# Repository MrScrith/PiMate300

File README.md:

# PiMate300

This is a project to upgrade an Apple eMate 300 to become a modern laptop, it will be powered by a Raspberry Pi to allow upgrade flexability (when a new Pi comes out it should be possible to upgrade the Pi and keep the existing board).

It will start with passive cooling, with an eye to adding a tiny fan to the Right side in case that is not viable.

Hopefully, all original openings will be used (with new inserts for different ports) and minimal case modification would be needed.

At the moment the following items will need to be modified/removed from the case: 
- Battery Box (unless a powerful LiPro or similar battery can be found to fit there).
- Center mounting post (for accessability and asthetics the Pi will be placed in the center).

## The following tools will be used for this project:
| Tool | Version | Purpose |
|------|---------|---------|
| [KiCad](https://www.kicad-pcb.org/) | v5.1.5 | PCB Design and layout |
| **TBD** | **TBD** | 3D Modeling of inserts and supports |
| **TBD** | **TBD** | Programming of microprocessor used for Power Management and Keyboard USB HID |
| [Quartus II](https://fpgasoftware.intel.com/13.0sp1/?edition=subscription) | v13.0 SP 1 | Programming of FPGA for display |

# Eventually this will be sold as an almost-drop-in kit, at least that is the hope.

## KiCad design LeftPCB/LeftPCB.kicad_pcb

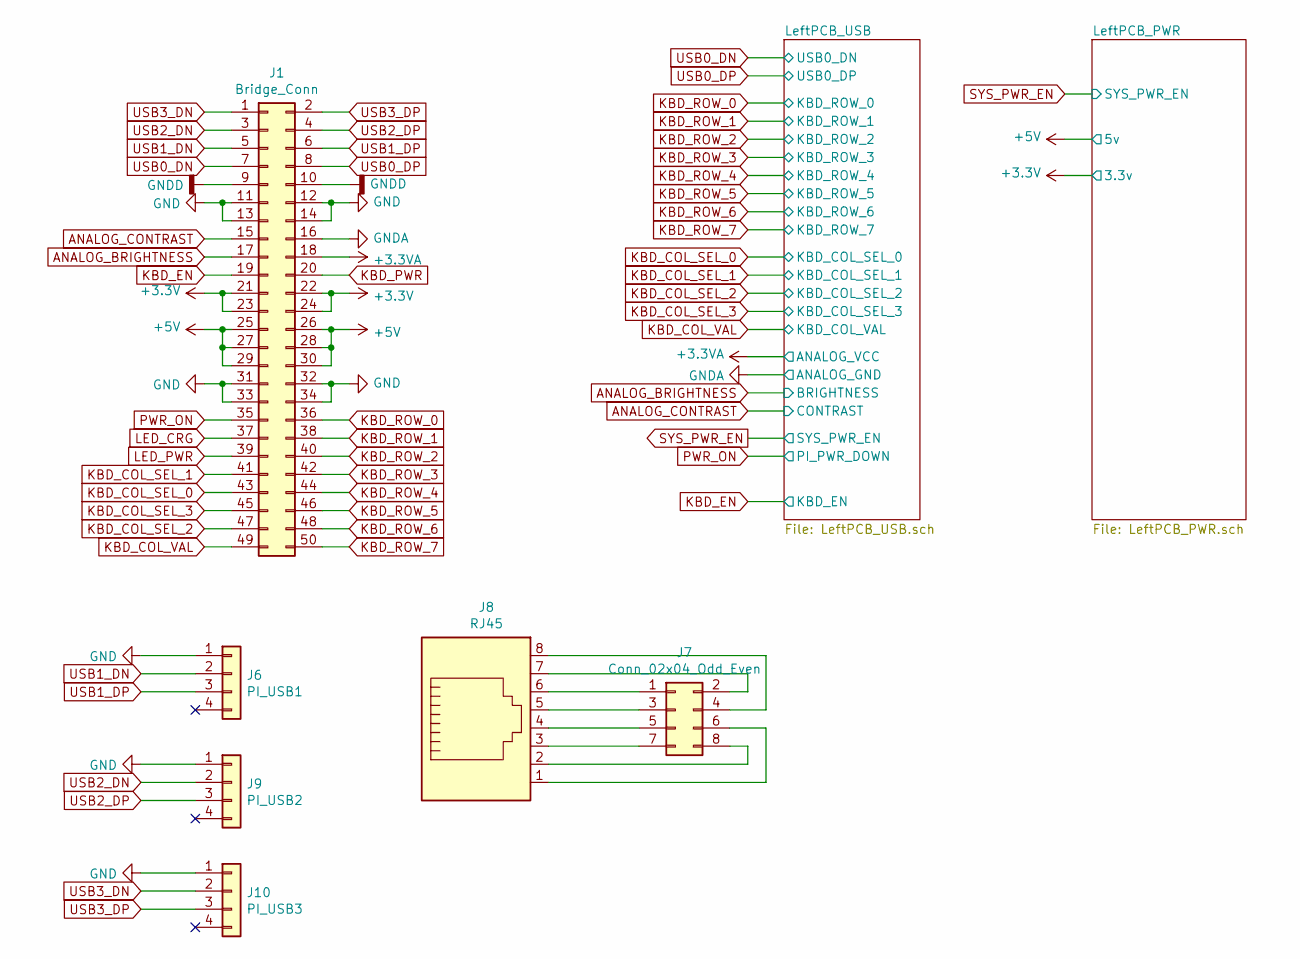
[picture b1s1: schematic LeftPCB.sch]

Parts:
J1: Bridge_Conn; Pin_Header_Straight_2x25_Pitch2.00mm
J6: PI_USB1; Pin_Header_Straight_1x04_Pitch1.00mm
J7: Conn_02x04_Odd_Even; Pin_Header_Straight_2x04_Pitch1.00mm
J8: RJ45; RJ45_8
J9: PI_USB2; Pin_Header_Straight_1x04_Pitch1.00mm
J10: PI_USB3; Pin_Header_Straight_1x04_Pitch1.00mm

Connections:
+3V3: J1.21, J1.22, J1.23, J1.24; also elsewhere on the board
+5V: J1.25, J1.26, J1.27, J1.28, J1.29, J1.30; also elsewhere on the board
ANALOG_BRIGHTNESS: J1.17; also elsewhere on the board
ANALOG_CONTRAST: J1.15; also elsewhere on the board
ANALOG_GND: J1.16; also elsewhere on the board
ANALOG_PWR: J1.18; also elsewhere on the board
GND: J1.11, J1.12, J1.13, J1.14, J1.31, J1.32, J1.33, J1.34, J6.1, J9.1, J10.1; also elsewhere on the board
GNDD: J1.9, J1.10; also elsewhere on the board
IS_PWR_DWN: J1.35; also elsewhere on the board
KBD_COL_SEL_0: J1.43; also elsewhere on the board
KBD_COL_SEL_1: J1.41; also elsewhere on the board
KBD_COL_SEL_2: J1.47; also elsewhere on the board
KBD_COL_SEL_3: J1.45; also elsewhere on the board
KBD_COL_VAL: J1.49; also elsewhere on the board
KBD_EN: J1.19; also elsewhere on the board
KBD_PWR: J1.20
KBD_ROW_0: J1.36; also elsewhere on the board
KBD_ROW_1: J1.38; also elsewhere on the board
KBD_ROW_2: J1.40; also elsewhere on the board
KBD_ROW_3: J1.42; also elsewhere on the board
KBD_ROW_4: J1.44; also elsewhere on the board
KBD_ROW_5: J1.46; also elsewhere on the board
KBD_ROW_6: J1.48; also elsewhere on the board
KBD_ROW_7: J1.50; also elsewhere on the board
LED_CRG: J1.37
LED_PWR: J1.39
unnamed: J7.1, J8.6
unnamed: J7.2, J8.7
unnamed: J7.3, J8.5
unnamed: J7.4, J8.8
unnamed: J7.5, J8.4
unnamed: J7.6, J8.1
unnamed: J7.7, J8.3
unnamed: J7.8, J8.2
USB0_DN: J1.7; also elsewhere on the board
USB0_DP: J1.8; also elsewhere on the board
USB1_DN: J1.5, J6.2
USB1_DP: J1.6, J6.3
USB2_DN: J1.3, J9.2
USB2_DP: J1.4, J9.3
USB3_DN: J1.1, J10.2
USB3_DP: J1.2, J10.3

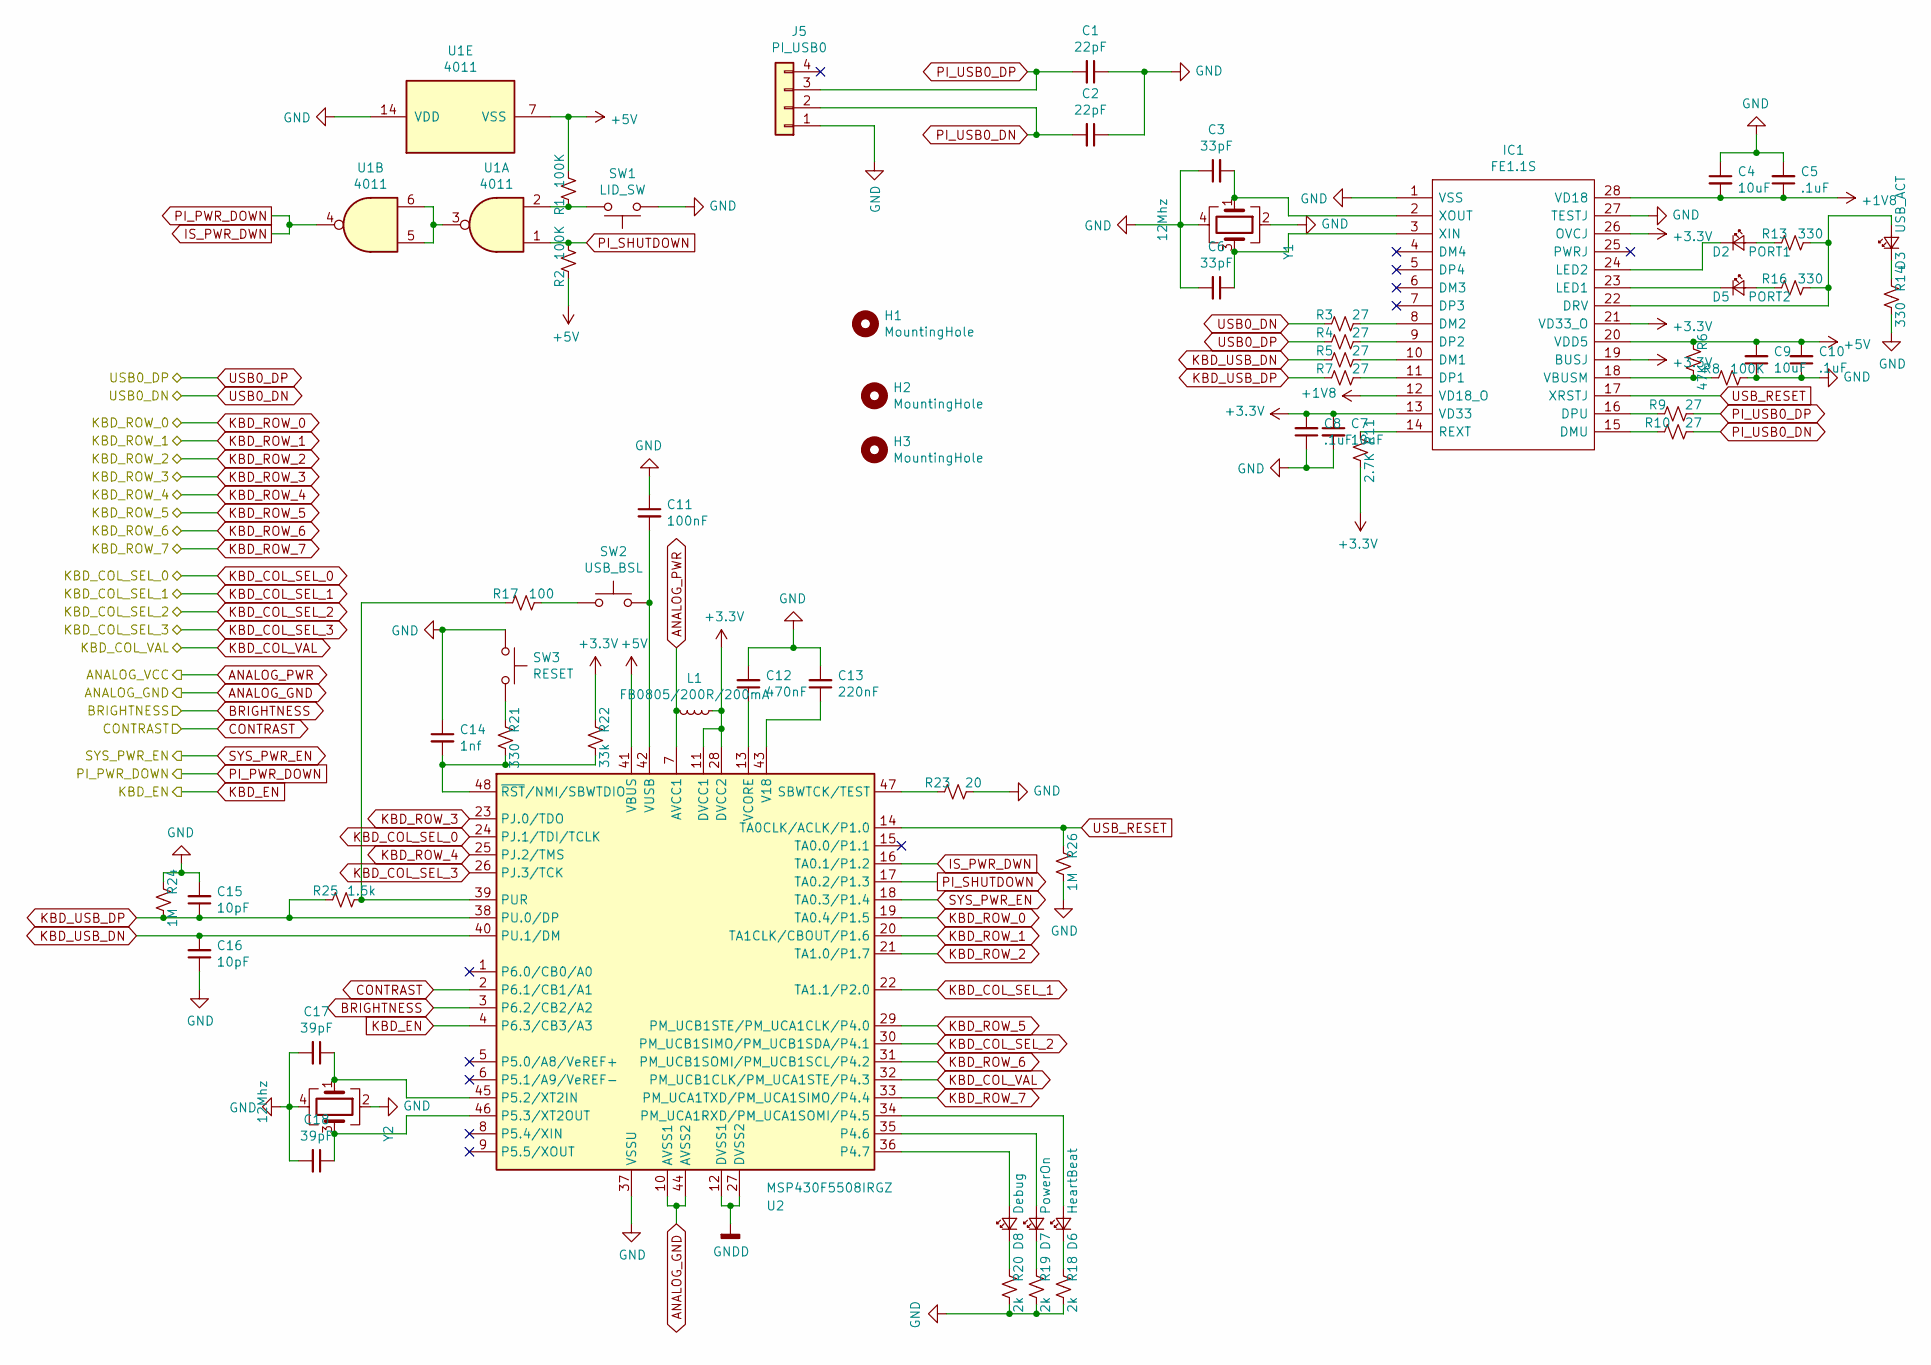
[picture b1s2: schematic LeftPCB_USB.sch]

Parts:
C1, C2: 22pF; C_0603
C3, C6: 33pF; C_0603
C4, C7, C9: 10uF; C_0603
C5, C8, C10: .1uF; C_0603
C11: 100nF; C_0603
C12: 470nF; C_0603
C13: 220nF; C_0603
C14: 1nf; C_0603
C15, C16: 10pF; C_0603
C17, C18: 39pF; C_0603
D2: PORT1; LED_0805
D3: USB_ACT; LED_0805
D5: PORT2; LED_0805
D6: HeartBeat; LED_0805
D7: PowerOn; LED_0805
D8: Debug; LED_0805
H1, H2, H3: MountingHole; MountingHole_2.7mm
IC1: FE1.1S; SOP64P600X175-28N; Manufacturer_Part_Number FE1.1S
J5: PI_USB0; Pin_Header_Straight_1x04_Pitch1.00mm
L1: FB0805/200R/200mA; L_0805
R1, R2, R8: 100K; R_0603
R3, R4, R5, R7, R9, R10: 27; R_0603
R6: 47K; R_0603
R11: 2.7K; R_0603
R13, R14, R16, R21: 330; R_0603
R17: 100; R_0603
R18, R19, R20: 2k; R_0603
R22: 33k; R_0603
R23: 20; R_0603
R24, R26: 1M; R_0603
R25: 1.5k; R_0603
SW1: LID_SW; SW_SPST_B3S-1000
SW2: USB_BSL; SW_SPST_B3S-1000
SW3: RESET; SW_SPST_B3S-1000
U1: 4011; SOIC-14_3.9x8.7mm_Pitch1.27mm
U2: MSP430F5508IRGZ; LQFP-48_7x7mm_Pitch0.5mm
Y1, Y2: 12Mhz; Oscillator_SMD_EuroQuartz_XO53-4pin_5.0x3.2mm

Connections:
+1V8: C4.2, C5.1, IC1.12 (VD18_O), IC1.28 (VD18)
+3V3: C7.1, C8.2, IC1.13 (VD33), IC1.19 (BUSJ), IC1.21 (VD33_O), IC1.26 (OVCJ), L1.1, R11.1, R22.2, U2.11 (DVCC1), U2.28 (DVCC2); also elsewhere on the board
+5V: C9.2, C10.2, IC1.20 (VDD5), R1.1, R2.2, R6.2, U1.7 (VSS), U2.41 (VBUS); also elsewhere on the board
ANALOG_BRIGHTNESS: U2.3 (P6.2/CB2/A2); also elsewhere on the board
ANALOG_CONTRAST: U2.2 (P6.1/CB1/A1); also elsewhere on the board
ANALOG_GND: U2.10 (AVSS1), U2.44 (AVSS2); also elsewhere on the board
ANALOG_PWR: L1.2, U2.7 (AVCC1); also elsewhere on the board
GND: C1.1, C2.1, C3.1, C4.1, C5.2, C6.2, C7.2, C8.1, C9.1, C10.1, C11.1, C12.2, C13.2, C14.1, C15.2, C16.1, C17.2, C18.2, IC1.1 (VSS), IC1.27 (TESTJ), J5.1, R8.1, R14.1, R18.1, R19.1, R20.1, R23.1, R24.2, R26.1, SW1.1, SW3.1, U1.14 (VDD), U2.37 (VSSU), Y1.2, Y1.4, Y2.2, Y2.4; also elsewhere on the board
GNDD: U2.12 (DVSS1), U2.27 (DVSS2); also elsewhere on the board
IS_PWR_DWN: U1.4, U2.16 (TA0.1/P1.2); also elsewhere on the board
KBD_COL_SEL_0: U2.24 (PJ.1/TDI/TCLK); also elsewhere on the board
KBD_COL_SEL_1: U2.22 (TA1.1/P2.0); also elsewhere on the board
KBD_COL_SEL_2: U2.30 (PM_UCB1SIMO/PM_UCB1SDA/P4.1); also elsewhere on the board
KBD_COL_SEL_3: U2.26 (PJ.3/TCK); also elsewhere on the board
KBD_COL_VAL: U2.32 (PM_UCB1CLK/PM_UCA1STE/P4.3); also elsewhere on the board
KBD_EN: U2.4 (P6.3/CB3/A3); also elsewhere on the board
KBD_ROW_0: U2.19 (TA0.4/P1.5); also elsewhere on the board
KBD_ROW_1: U2.20 (TA1CLK/CBOUT/P1.6); also elsewhere on the board
KBD_ROW_2: U2.21 (TA1.0/P1.7); also elsewhere on the board
KBD_ROW_3: U2.23 (PJ.0/TDO); also elsewhere on the board
KBD_ROW_4: U2.25 (PJ.2/TMS); also elsewhere on the board
KBD_ROW_5: U2.29 (PM_UCB1STE/PM_UCA1CLK/P4.0); also elsewhere on the board
KBD_ROW_6: U2.31 (PM_UCB1SOMI/PM_UCB1SCL/P4.2); also elsewhere on the board
KBD_ROW_7: U2.33 (PM_UCA1TXD/PM_UCA1SIMO/P4.4); also elsewhere on the board
KBD_USB_DN: C16.2, R5.2, U2.40 (PU.1/DM)
KBD_USB_DP: C15.1, R7.2, R24.1, R25.2, U2.38 (PU.0/DP)
unnamed: C3.2, IC1.2 (XOUT), Y1.1
unnamed: C6.1, IC1.3 (XIN), Y1.3
unnamed: C11.2, SW2.2, U2.42 (VUSB)
unnamed: C12.1, U2.13 (VCORE)
unnamed: C13.1, U2.43 (V18)
unnamed: C14.2, R21.1, R22.1, U2.48 (~RST~/NMI/SBWTDIO)
unnamed: C17.1, U2.45 (P5.2/XT2IN), Y2.1
unnamed: C18.1, U2.46 (P5.3/XT2OUT), Y2.3
unnamed: D2.1 (K), IC1.24 (LED2)
unnamed: D2.2 (A), R13.2
unnamed: D3.1 (K), R14.2
unnamed: D3.2 (A), IC1.22 (DRV), R13.1, R16.1
unnamed: D5.1 (K), IC1.23 (LED1)
unnamed: D5.2 (A), R16.2
unnamed: D6.1 (K), R18.2
unnamed: D6.2 (A), U2.34 (PM_UCA1RXD/PM_UCA1SOMI/P4.5)
unnamed: D7.1 (K), R19.2
unnamed: D7.2 (A), U2.35 (P4.6)
unnamed: D8.1 (K), R20.2
unnamed: D8.2 (A), U2.36 (P4.7)
unnamed: IC1.8 (DM2), R3.1
unnamed: IC1.9 (DP2), R4.1
unnamed: IC1.10 (DM1), R5.1
unnamed: IC1.11 (DP1), R7.1
unnamed: IC1.14 (REXT), R11.2
unnamed: IC1.15 (DMU), R10.2
unnamed: IC1.16 (DPU), R9.2
unnamed: IC1.18 (VBUSM), R6.1, R8.2
unnamed: R1.2, SW1.2, U1.2
unnamed: R17.1, SW2.1
unnamed: R17.2, R25.1, U2.39 (PUR)
unnamed: R21.2, SW3.2
unnamed: R23.2, U2.47 (SBWTCK/TEST)
unnamed: U1.3, U1.5, U1.6
PI_SHUTDOWN: R2.1, U1.1, U2.17 (TA0.2/P1.3)
PI_USB0_DN: C2.2, J5.2, R10.1
PI_USB0_DP: C1.2, J5.3, R9.1
SYS_PWR_EN: U2.18 (TA0.3/P1.4); also elsewhere on the board
USB0_DN: R3.2; also elsewhere on the board
USB0_DP: R4.2; also elsewhere on the board
USB_RESET: IC1.17 (XRSTJ), R26.2, U2.14 (TA0CLK/ACLK/P1.0)

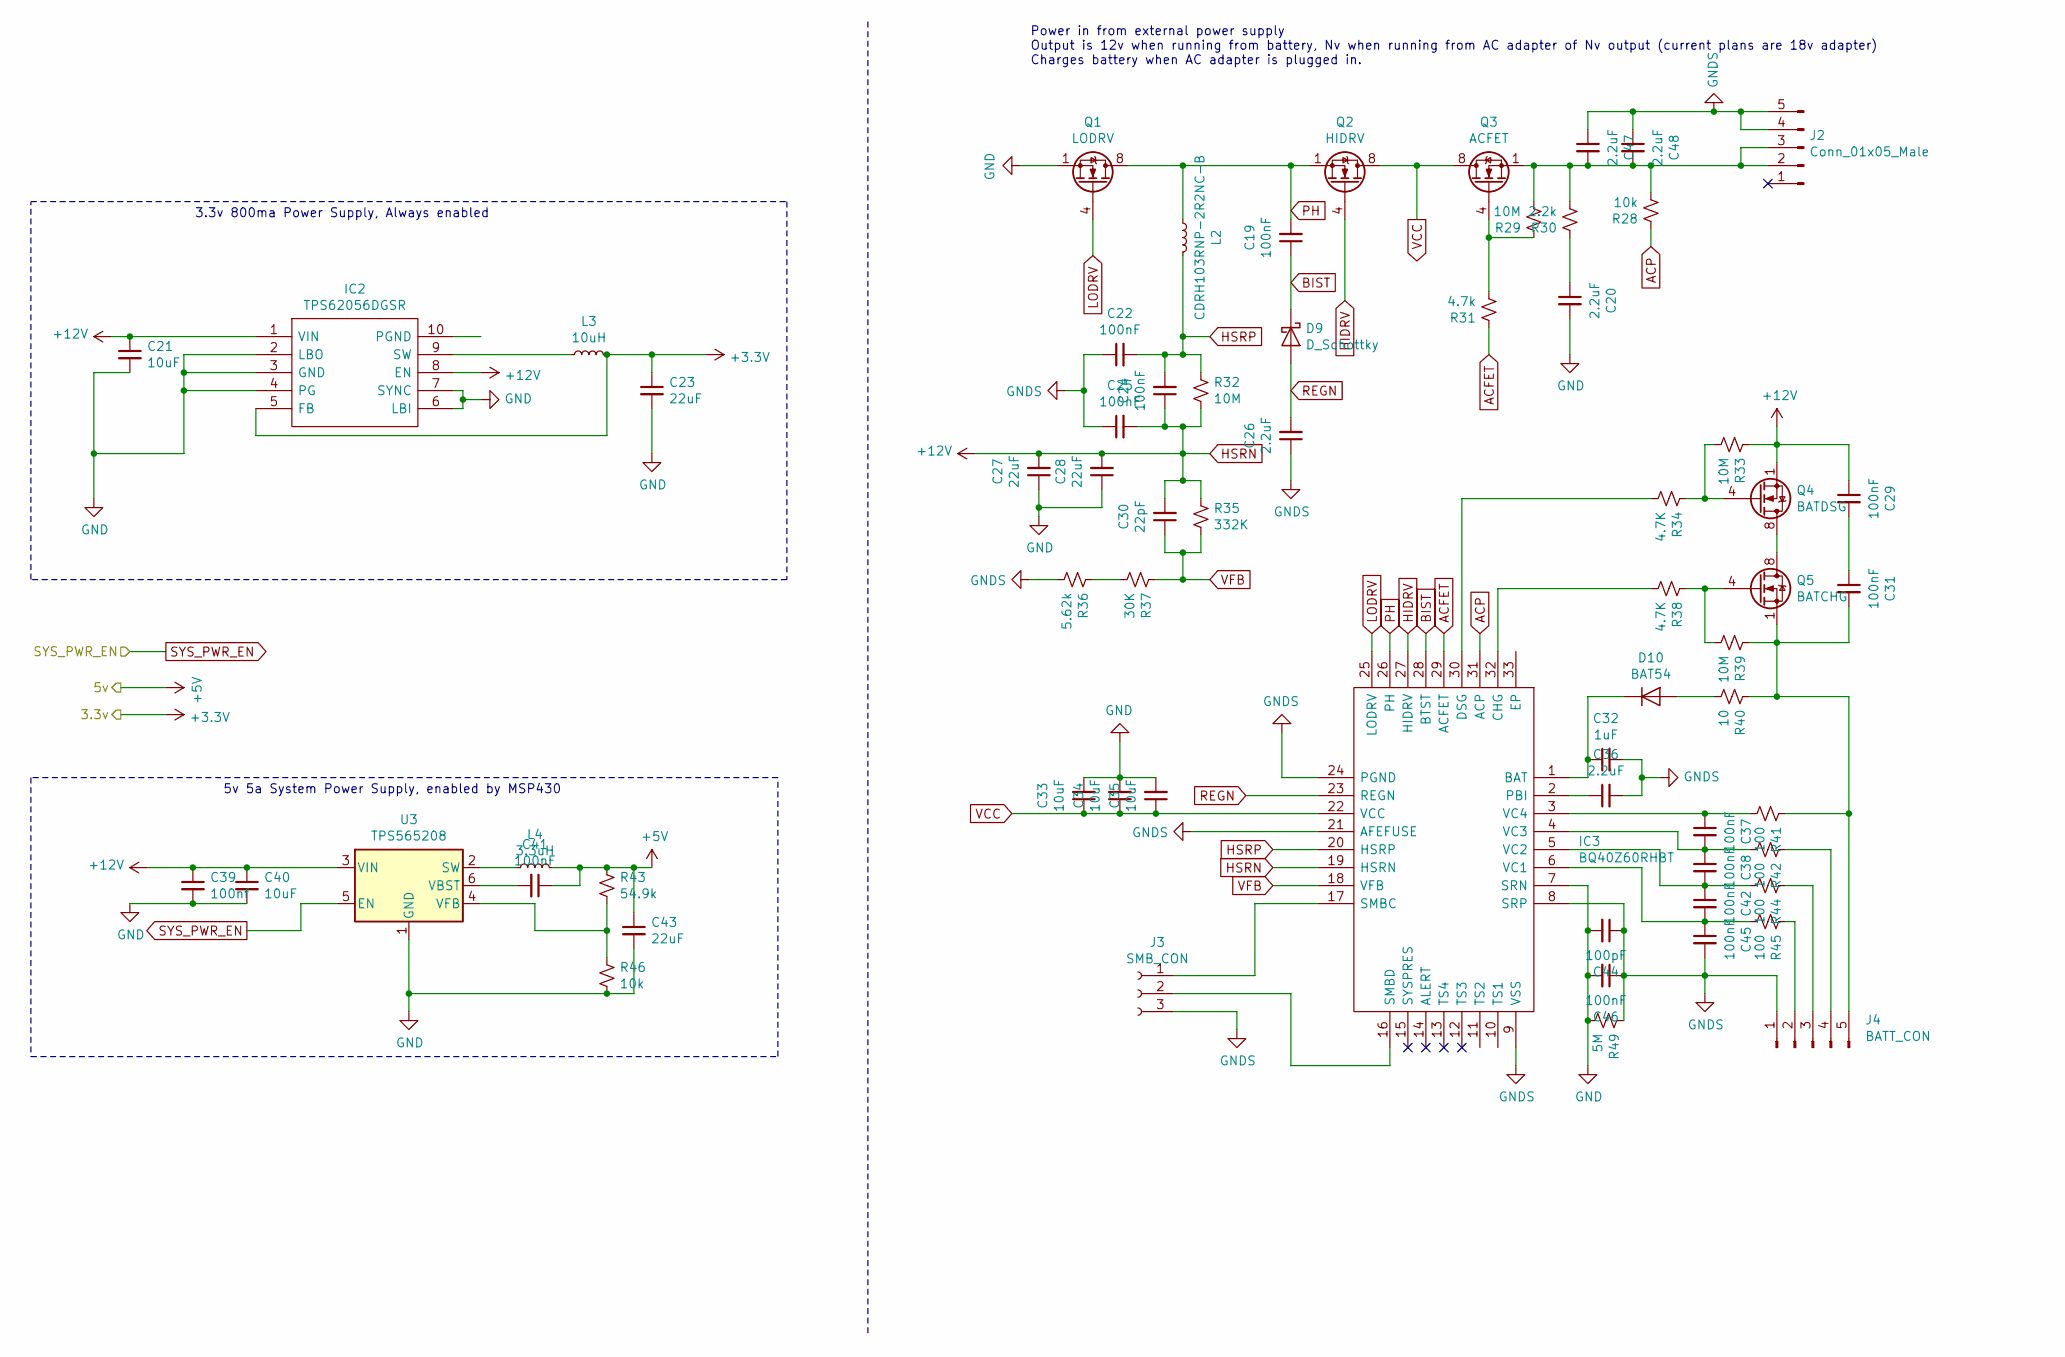
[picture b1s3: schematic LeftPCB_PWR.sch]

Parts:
C19, C22, C24, C25, C29, C31, C37, C38, C41, C42, C45, C46: 100nF; C_0603
C20, C26, C36, C47, C48: 2.2uF; C_0603
C21, C33, C34, C35, C40: 10uF; C_0603
C23, C27, C28, C43: 22uF; C_0603
C30: 22pF; C_0603
C32: 1uF; C_0603
C39: 100nf; C_0603
C44: 100pF; C_0603
D9: D_Schottky; D_0603
D10: BAT54; D_0603
IC2: TPS62056DGSR; SOP50P490X110-10N; Manufacturer_Part_Number TPS62056DGSR; Mouser Part Number 595-TPS62056DGSR
IC3: BQ40Z60RHBT; QFN50P500X500X100-33N-D; Manufacturer_Part_Number BQ40Z60RHBT; Mouser Part Number 595-BQ40Z60RHBT
J2: Conn_01x05_Male; Pin_Header_Straight_1x05_Pitch1.00mm
J3: SMB_CON; Pin_Header_Straight_1x03_Pitch1.00mm
J4: BATT_CON; Pin_Header_Straight_1x05_Pitch1.00mm
L2: CDRH103RNP-2R2NC-B; L_Vishay_IHLP-2020
L3: 10uH; L_0603
L4: 3.3uH; L_0603
Q1: LODRV; SOIC-8-N
Q2: HIDRV; SOIC-8-N
Q3: ACFET; SOIC-8-N
Q4: BATDSG; SOIC-8-N
Q5: BATCHG; SOIC-8-N
R28, R46: 10k; R_0603
R29, R32, R33, R39: 10M; R_0603
R30: 2.2k; R_0603
R31: 4.7k; R_0603
R34, R38: 4.7K; R_0603
R35: 332K; R_0603
R36: 5.62k; R_0603
R37: 30K; R_0603
R40: 10; R_0603
R41, R42, R44, R45: 100; R_0603
R43: 54.9k; R_0603
R49: 5M; R_2010
U3: TPS565208; SOT95P280X110-6N

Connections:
+3V3: C23.1, IC2.5 (FB), L3.2; also elsewhere on the board
+5V: C41.1, C43.1, L4.2, R43.2; also elsewhere on the board
ACFET: IC3.29 (ACFET), R31.1
ACP: IC3.31 (ACP), R28.1
BIST: C19.1, D9.1 (K), IC3.28 (BTST)
GND: C20.2, C21.2, C23.2, C27.1, C28.1, C33.2, C34.2, C35.2, C39.2, C40.2, C43.2, C44.2, C46.2, IC2.2 (LBO), IC2.3 (GND), IC2.4 (PG), IC2.6 (LBI), IC2.7 (SYNC), IC3.7 (SRN), Q1.1 (S), Q1.2 (S), Q1.3 (S), R46.1, R49.2, U3.1 (GND); also elsewhere on the board
GNDS: C22.1, C25.1, C26.1, C32.2, C36.2, C44.1, C45.2, C46.1, C47.1, C48.1, IC3.8 (SRP), IC3.9 (VSS), IC3.21 (AFEFUSE), IC3.24 (PGND), J2.4, J2.5, J3.3, J4.1, R36.2, R49.1
HIDRV: IC3.27 (HIDRV), Q2.4 (G)
HSRN: C21.1, C24.1, C25.2, C27.2, C28.2, C29.1, C30.2, C39.1, C40.1, IC2.1 (VIN), IC2.8 (EN), IC3.19 (HSRN), Q4.1 (S), Q4.2 (S), Q4.3 (S), R32.2, R33.1, R35.1, U3.3 (VIN)
HSRP: C22.2, C24.2, IC3.20 (HSRP), L2.2, R32.1
LODRV: IC3.25 (LODRV), Q1.4 (G)
unnamed: C20.1, R30.1
unnamed: C29.2, C31.1
unnamed: C31.2, J4.5, Q5.1 (S), Q5.2 (S), Q5.3 (S), R39.1, R40.1, R41.1
unnamed: C32.1, D10.1 (K), IC3.1 (BAT)
unnamed: C36.1, IC3.2 (PBI)
unnamed: C37.1, IC3.3 (VC4), R41.2
unnamed: C37.2, C38.1, IC3.4 (VC3), R42.2
unnamed: C38.2, C42.1, IC3.5 (VC2), R44.2
unnamed: C41.2, U3.6 (VBST)
unnamed: C42.2, C45.1, IC3.6 (VC1), R45.2
unnamed: C47.2, C48.2, J2.2, J2.3, Q3.1 (S), Q3.2 (S), Q3.3 (S), R28.2, R29.2, R30.2
unnamed: D10.2 (A), R40.2
unnamed: IC2.9 (SW), L3.1
unnamed: IC3.16 (SMBD), J3.2
unnamed: IC3.17 (SMBC), J3.1
unnamed: IC3.30 (DSG), R34.2
unnamed: IC3.32 (CHG), R38.2
unnamed: J4.2, R45.1
unnamed: J4.3, R44.1
unnamed: J4.4, R42.1
unnamed: L4.1, U3.2 (SW)
unnamed: Q3.4 (G), R29.1, R31.2
unnamed: Q4.4 (G), R33.2, R34.1
unnamed: Q4.5 (D), Q4.6 (D), Q4.7 (D), Q4.8 (D), Q5.5 (D), Q5.6 (D), Q5.7 (D), Q5.8 (D)
unnamed: Q5.4 (G), R38.1, R39.2
unnamed: R36.1, R37.2
unnamed: R43.1, R46.2, U3.4 (VFB)
PH: C19.2, IC3.26 (PH), L2.1, Q1.5 (D), Q1.6 (D), Q1.7 (D), Q1.8 (D), Q2.1 (S), Q2.2 (S), Q2.3 (S)
REGN: C26.2, D9.2 (A), IC3.23 (REGN)
SYS_PWR_EN: U3.5 (EN); also elsewhere on the board
VCC: C33.1, C34.1, C35.1, IC3.22 (VCC), Q2.5 (D), Q2.6 (D), Q2.7 (D), Q2.8 (D), Q3.5 (D), Q3.6 (D), Q3.7 (D), Q3.8 (D)
VFB: C30.1, IC3.18 (VFB), R35.2, R37.1

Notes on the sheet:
Power in from external power supply Output is 12v when running from battery, Nv when running from AC adapter of Nv output (current plans are 18v adapter) Charges battery when AC adapter is plugged in.
5v 5a System Power Supply, enabled by MSP430
3.3v 800ma Power Supply, Always enabled

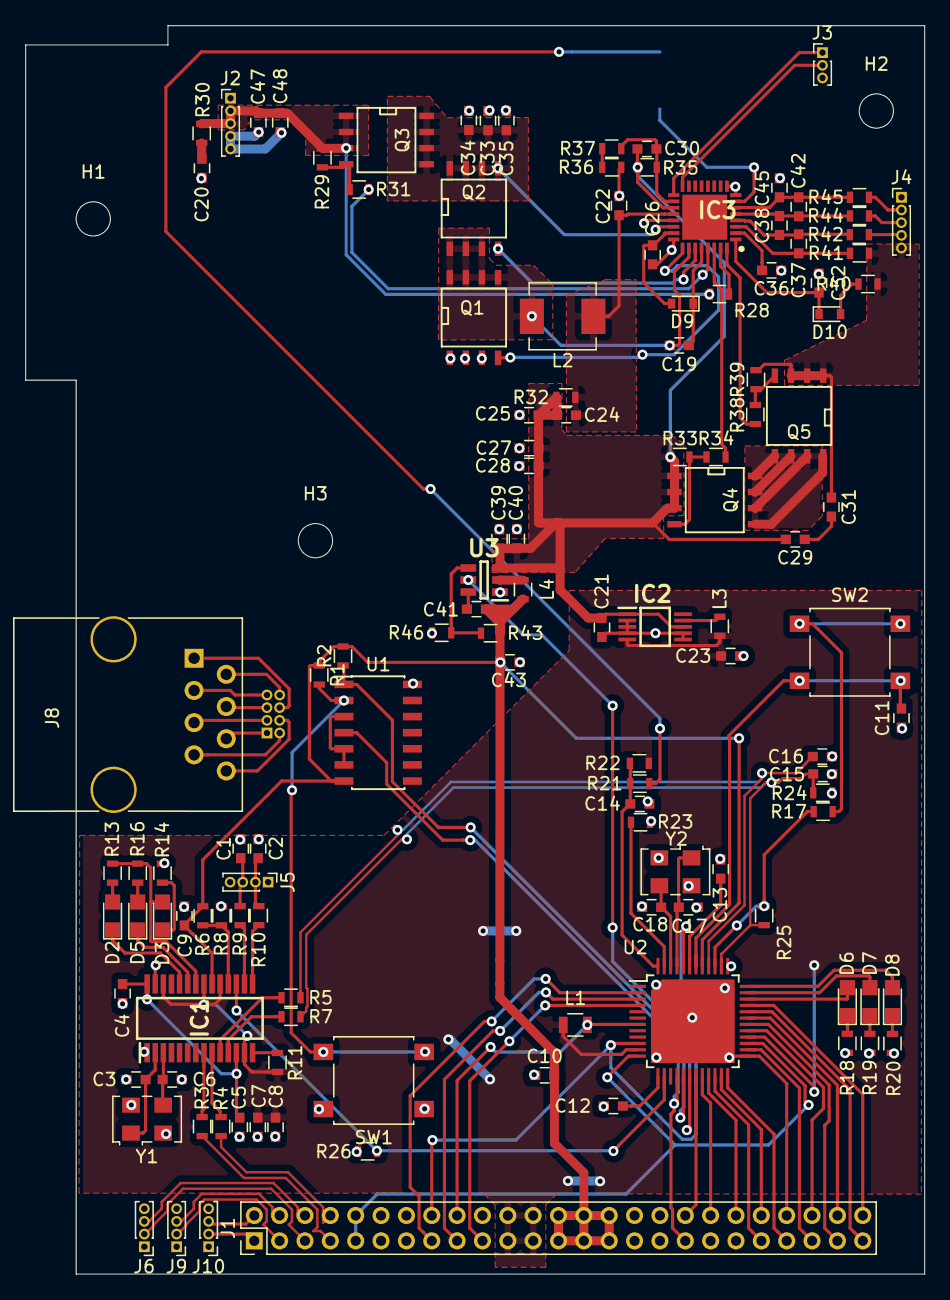
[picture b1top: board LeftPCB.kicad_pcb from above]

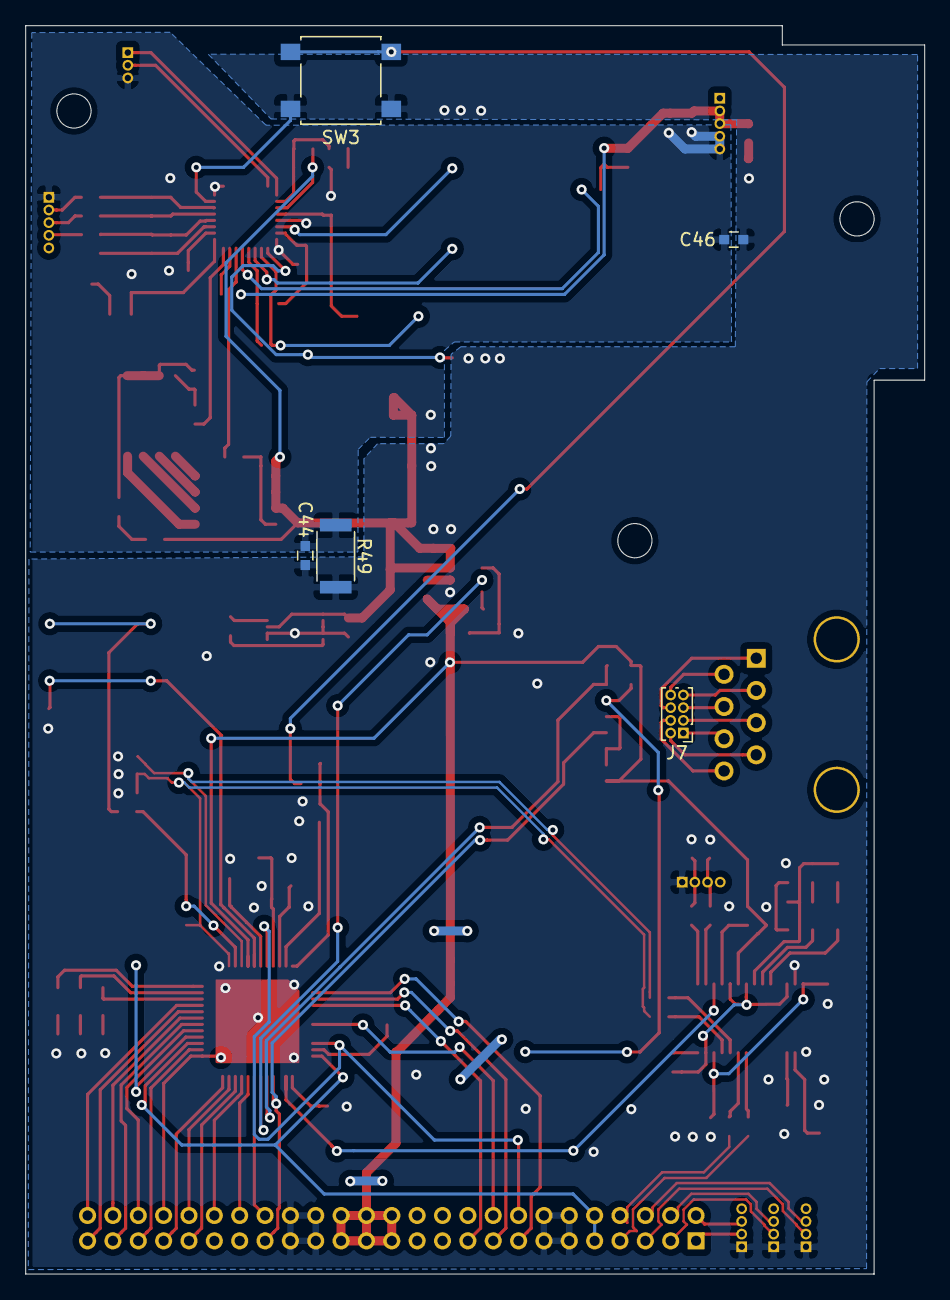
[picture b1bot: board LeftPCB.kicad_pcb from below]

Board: 2 copper layers, 70.9 x 98.5 mm, 133 parts (5 on the bottom side), 120 nets.

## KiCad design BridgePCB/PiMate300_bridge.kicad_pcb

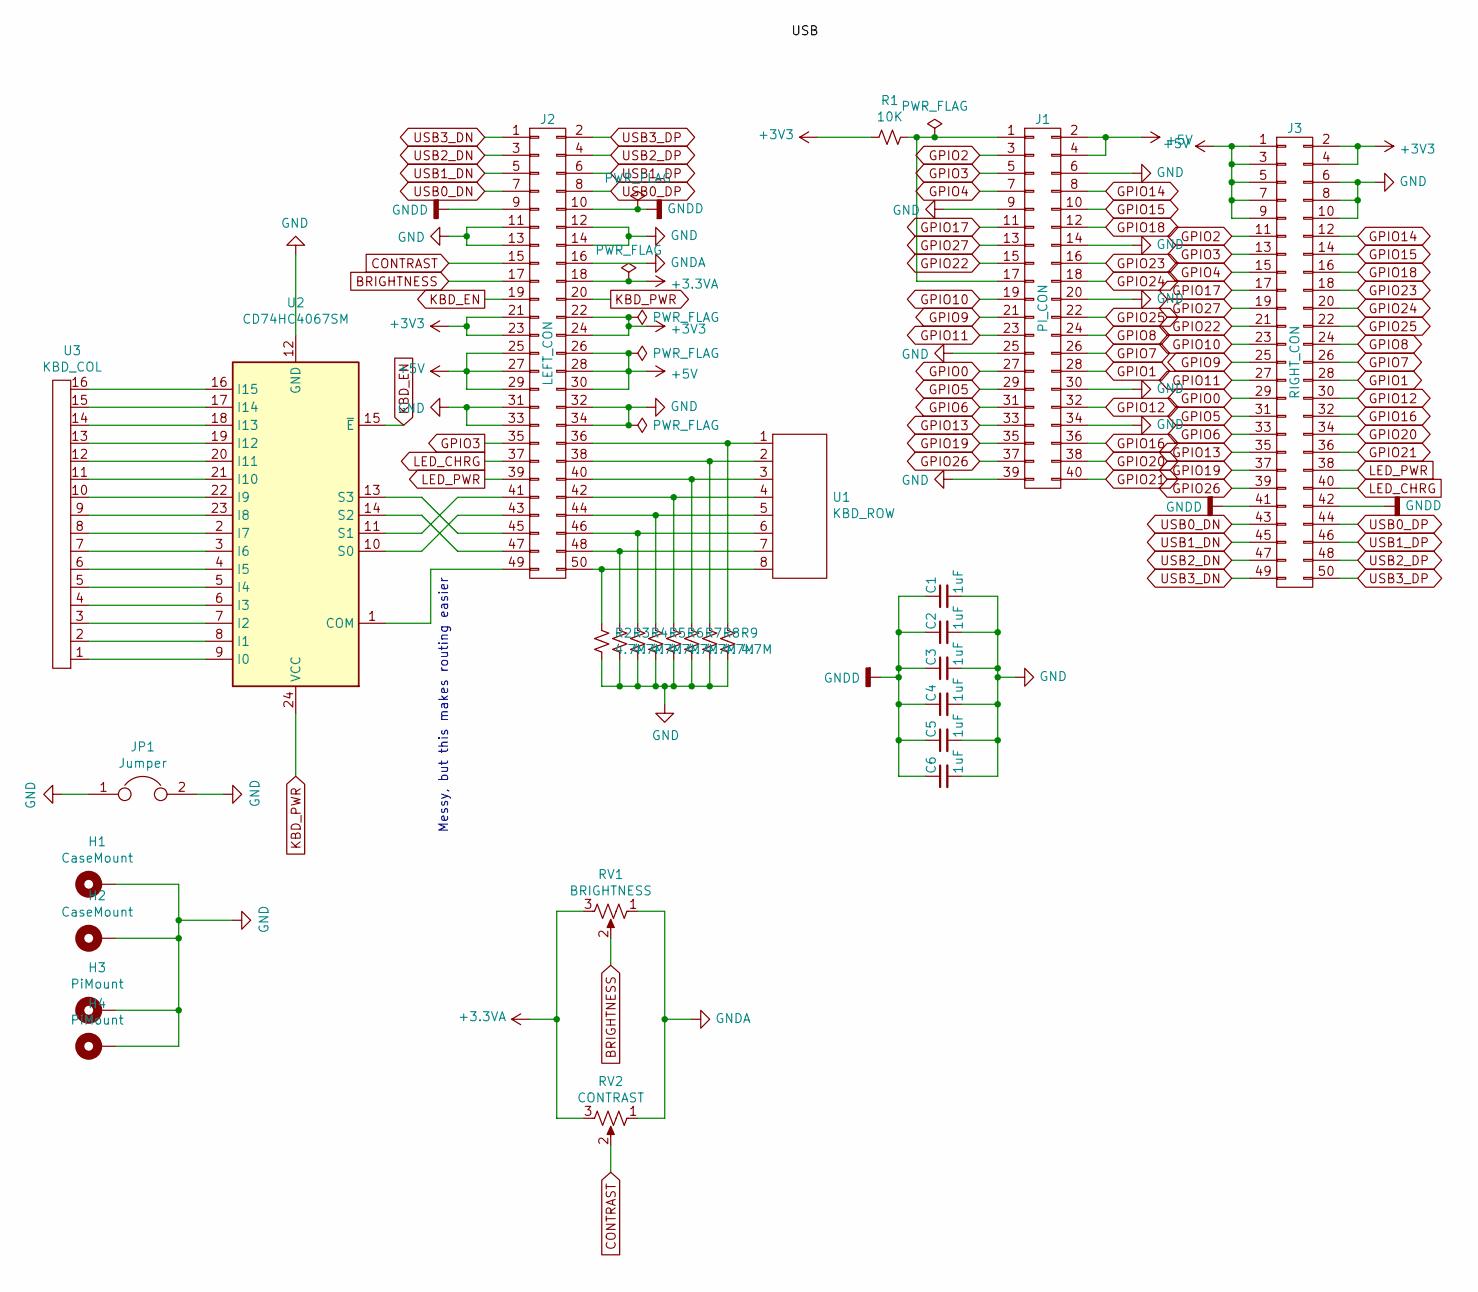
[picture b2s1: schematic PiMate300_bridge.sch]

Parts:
C1, C2, C3, C4, C5, C6: 1uF; C_0603_HandSoldering
H1, H2: CaseMount; MountingHole_3.2mm_M3_DIN965
H3, H4: PiMount; MountingHole_2.7mm_Pad
J1: PI_CON; Socket_Strip_Straight_2x20_Pitch2.54mm
J2: LEFT_CON; Socket_Strip_Angled_2x25_Pitch2.00mm
J3: RIGHT_CON; Socket_Strip_Angled_2x25_Pitch2.00mm
JP1: Jumper; NetTie-I
R1: 10K; R_0603_HandSoldering
R2, R3, R4, R5, R6, R7, R8, R9: 4.7M; R_0603_HandSoldering
RV1: BRIGHTNESS; PTA1543
RV2: CONTRAST; PTA1543
U1: KBD_ROW; FH12-08S-1SH
U2: CD74HC4067SM; CD74HC4067
U3: KBD_COL; FH12-16S-1SH

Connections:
+3.3VA: J2.18, RV1.3, RV2.3
+3V3: J2.21, J2.22, J2.23, J2.24, J3.2, J3.4, R1.2
+5V: J1.2, J1.4, J2.25, J2.26, J2.27, J2.28, J2.29, J2.30, J3.1, J3.3, J3.5, J3.7, J3.9
BRIGHTNESS: J2.17, RV1.2
CONTRAST: J2.15, RV2.2
GND: C1.2, C2.2, C3.2, C4.2, C5.2, C6.2, H1.1, H2.1, H3.1, H4.1, J1.6, J1.9, J1.14, J1.20, J1.25, J1.30, J1.34, J1.39, J2.11, J2.12, J2.13, J2.14, J2.31, J2.32, J2.33, J2.34, J3.6, J3.8, J3.10, JP1.1, JP1.2, R2.2, R3.2, R4.2, R5.2, R6.2, R7.2, R8.2, R9.2, U2.12 (GND)
GNDA: J2.16, RV1.1, RV2.1
GNDD: C1.1, C2.1, C3.1, C4.1, C5.1, C6.1, J2.9, J2.10, J3.41, J3.42
GPIO0: J1.27, J3.29
GPIO1: J1.28, J3.28
GPIO2: J1.3, J3.11
GPIO3: J1.5, J2.35, J3.13
GPIO4: J1.7, J3.15
GPIO5: J1.29, J3.31
GPIO6: J1.31, J3.33
GPIO7: J1.26, J3.26
GPIO8: J1.24, J3.24
GPIO9: J1.21, J3.25
GPIO10: J1.19, J3.23
GPIO11: J1.23, J3.27
GPIO12: J1.32, J3.30
GPIO13: J1.33, J3.35
GPIO14: J1.8, J3.12
GPIO15: J1.10, J3.14
GPIO16: J1.36, J3.32
GPIO17: J1.11, J3.17
GPIO18: J1.12, J3.16
GPIO19: J1.35, J3.37
GPIO20: J1.38, J3.34
GPIO21: J1.40, J3.36
GPIO22: J1.15, J3.21
GPIO23: J1.16, J3.18
GPIO24: J1.18, J3.20
GPIO25: J1.22, J3.22
GPIO26: J1.37, J3.39
GPIO27: J1.13, J3.19
KBD_EN: J2.19, U2.15 (~E)
KBD_PWR: J2.20, U2.24 (VCC)
LED_CHRG: J2.37, J3.40
LED_PWR: J2.39, J3.38
unnamed: J1.1, J1.17, R1.1
unnamed: J2.36, R9.1, U1.1
unnamed: J2.38, R8.1, U1.2
unnamed: J2.40, R7.1, U1.3
unnamed: J2.41, U2.11 (S1)
unnamed: J2.42, R6.1, U1.4
unnamed: J2.43, U2.10 (S0)
unnamed: J2.44, R5.1, U1.5
unnamed: J2.45, U2.13 (S3)
unnamed: J2.46, R4.1, U1.6
unnamed: J2.47, U2.14 (S2)
unnamed: J2.48, R3.1, U1.7
unnamed: J2.49, U2.1 (COM)
unnamed: J2.50, R2.1, U1.8
unnamed: U2.2 (I7), U3.8
unnamed: U2.3 (I6), U3.7
unnamed: U2.4 (I5), U3.6
unnamed: U2.5 (I4), U3.5
unnamed: U2.6 (I3), U3.4
unnamed: U2.7 (I2), U3.3
unnamed: U2.8 (I1), U3.2
unnamed: U2.9 (I0), U3.1
unnamed: U2.16 (I15), U3.16
unnamed: U2.17 (I14), U3.15
unnamed: U2.18 (I13), U3.14
unnamed: U2.19 (I12), U3.13
unnamed: U2.20 (I11), U3.12
unnamed: U2.21 (I10), U3.11
unnamed: U2.22 (I9), U3.10
unnamed: U2.23 (I8), U3.9
USB0_DN: J2.7, J3.43
USB0_DP: J2.8, J3.44
USB1_DN: J2.5, J3.45
USB1_DP: J2.6, J3.46
USB2_DN: J2.3, J3.47
USB2_DP: J2.4, J3.48
USB3_DN: J2.1, J3.49
USB3_DP: J2.2, J3.50

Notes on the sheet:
Messy, but this makes routing easier

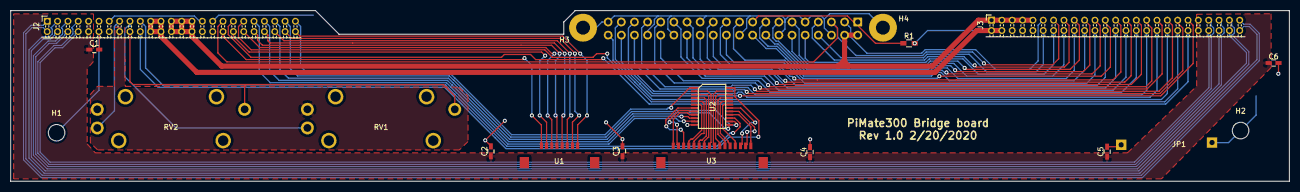
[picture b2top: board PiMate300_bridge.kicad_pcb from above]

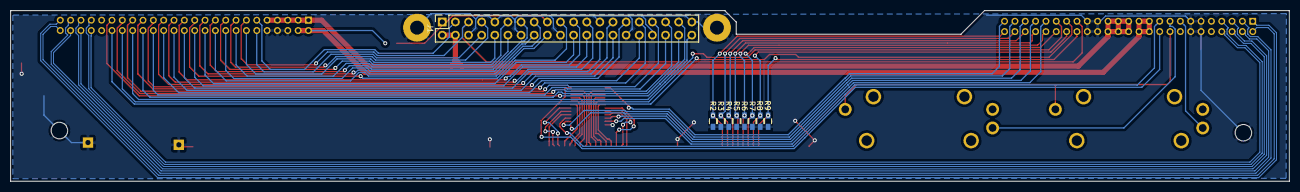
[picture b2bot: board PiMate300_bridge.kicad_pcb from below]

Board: 2 copper layers, 247.3 x 33.0 mm, 28 parts (9 on the bottom side), 78 nets.

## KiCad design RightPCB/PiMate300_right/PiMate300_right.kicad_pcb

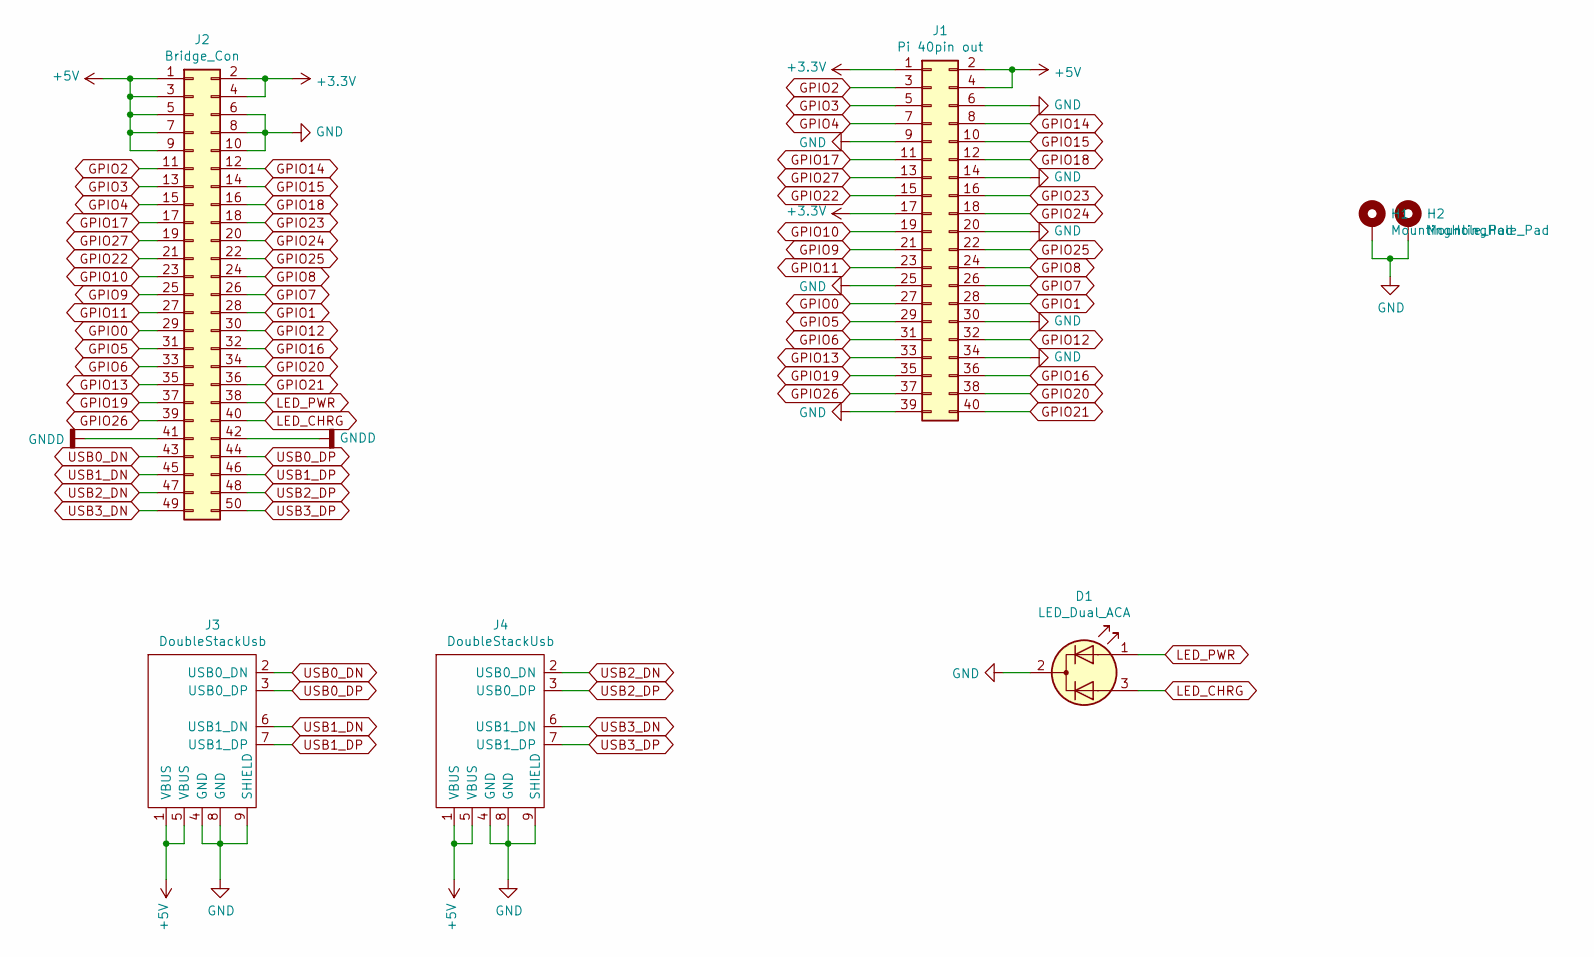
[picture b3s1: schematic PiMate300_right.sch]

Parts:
D1: LED_Dual_ACA; LED_D3.0mm-3
H1, H2: MountingHole_Pad; MountingHole_2.7mm_M2.5_DIN965_Pad
J1: Pi 40pin out; Socket_Strip_Straight_2x20_Pitch2.00mm
J2: Bridge_Con; Socket_Strip_Straight_2x25_Pitch2.00mm
J3, J4: DoubleStackUsb; USB_A_Double_Stack

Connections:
+3V3: J1.1, J1.17, J2.2, J2.4
+5V: J1.2, J1.4, J2.1, J2.3, J2.5, J2.7, J2.9, J3.1 (VBUS), J3.5 (VBUS), J4.1 (VBUS), J4.5 (VBUS)
GND: D1.2 (K), H1.1, H2.1, J1.6, J1.9, J1.14, J1.20, J1.25, J1.30, J1.34, J1.39, J2.6, J2.8, J2.10, J3.4 (GND), J3.8 (GND), J3.9 (SHIELD), J4.4 (GND), J4.8 (GND), J4.9 (SHIELD)
GNDD: J2.41, J2.42
GPIO0: J1.27, J2.29
GPIO1: J1.28, J2.28
GPIO2: J1.3, J2.11
GPIO3: J1.5, J2.13
GPIO4: J1.7, J2.15
GPIO5: J1.29, J2.31
GPIO6: J1.31, J2.33
GPIO7: J1.26, J2.26
GPIO8: J1.24, J2.24
GPIO9: J1.21, J2.25
GPIO10: J1.19, J2.23
GPIO11: J1.23, J2.27
GPIO12: J1.32, J2.30
GPIO13: J1.33, J2.35
GPIO14: J1.8, J2.12
GPIO15: J1.10, J2.14
GPIO16: J1.36, J2.32
GPIO17: J1.11, J2.17
GPIO18: J1.12, J2.16
GPIO19: J1.35, J2.37
GPIO20: J1.38, J2.34
GPIO21: J1.40, J2.36
GPIO22: J1.15, J2.21
GPIO23: J1.16, J2.18
GPIO24: J1.18, J2.20
GPIO25: J1.22, J2.22
GPIO26: J1.37, J2.39
GPIO27: J1.13, J2.19
LED_CHRG: D1.3 (A2), J2.40
LED_PWR: D1.1 (A1), J2.38
USB0_DN: J2.43, J3.2 (USB0_DN)
USB0_DP: J2.44, J3.3 (USB0_DP)
USB1_DN: J2.45, J3.6 (USB1_DN)
USB1_DP: J2.46, J3.7 (USB1_DP)
USB2_DN: J2.47, J4.2 (USB0_DN)
USB2_DP: J2.48, J4.3 (USB0_DP)
USB3_DN: J2.49, J4.6 (USB1_DN)
USB3_DP: J2.50, J4.7 (USB1_DP)

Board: 2 copper layers, 7 parts (0 on the bottom side), 42 nets, no tracks yet.

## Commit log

2020-02-20 Initial commit of PiMate 300 project, many hours into bridge board already.
2020-02-20 Updated readme with more project info
2020-02-21 Moved things around to handle multiple parts in the same repo.
2020-02-21 Started work on Right PCB, added model for double stack USB and started positioning.
2020-02-27 Started work on Left PCB Schematics.
2020-02-28 Updated schematic for LeftPCB, completed USB hub and Keyboard HID device, and started work on the power supply have the external, 3.3v, and 5v mapped out, just need to figure out battery charging/usa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
2020-03-06 Completed most of left side schematic and started working on layout.
2020-03-13 Updated and performed layout on most of left PCB, still have a few things to add.
